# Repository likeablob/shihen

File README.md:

**SHIHEN** is a device which colors your everyday (a bit).  
Have a glimpse of your favorite poems, quotes or scenes of a movie.

## Features
- On board RTC offers 2+ years of battery life.([in theory](https://blc.now.sh/?config=eyJiYXR0ZXJ5Q2FwYWNpdHkiOiIzNTAiLCJzbGVlcEN1cnJlbnRNaWxpcyI6MC4wMDUsIndha2VDdXJyZW50TWlsaXMiOiI4MCIsIndha2V1cENvdW50IjoiMTIiLCJ3YWtldXBVbml0Ijo4NjQwMCwid2FrZXVwU2VjIjoiMSJ9))
- By using [a dedicated Web-based converter](https://shihen.now.sh/), you can quickly show any texts and videos on the device.

## Gallery
|    |  |
| :------------------------------------------------------------------------------: | :----------------------------------------------------------------------------: |
|  |  |
|    |                                                                                |

## Project structure
- [`pio/`](./pio) - code for the firmware(PlatformIO)
- [`kicad/`](./kicad) - PCB design (KiCad)
- [`openscad/`](./openscad) - models for the 3D-printable case. (OpenSCAD)
- https://github.com/likeablob/shihen-webui - code for the WebUI(Nuxt.js + Vuetify)

## Build Instructions
WIP

## BOM
WIP

## Refs
- Hackaday.io: https://hackaday.io/project/168039-shihen

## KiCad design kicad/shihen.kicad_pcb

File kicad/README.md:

# SHIHEN/PCB

## Prerequisites
- [KiCAD](http://kicad-pcb.org/) v5.0.1

## Credits
- [jdunmire]'s [ESP-12E.kicad_mod](./lib_ext/ESP-12E.kicad_mod): borrowed from [jdunmire/kicad-ESP8266](https://github.com/jdunmire/kicad-ESP8266/tree/70e6530de5e3cae4ae77a4bca7d73b20a0af6baf)
- [Joan_Sparky]'s [Conn_uSDcard.kicad_mod](./lib_ext/Conn_uSDcard.kicad_mod): borrowed from  https://forum.kicad.info/t/microsd-component-footprint-help/3095/5

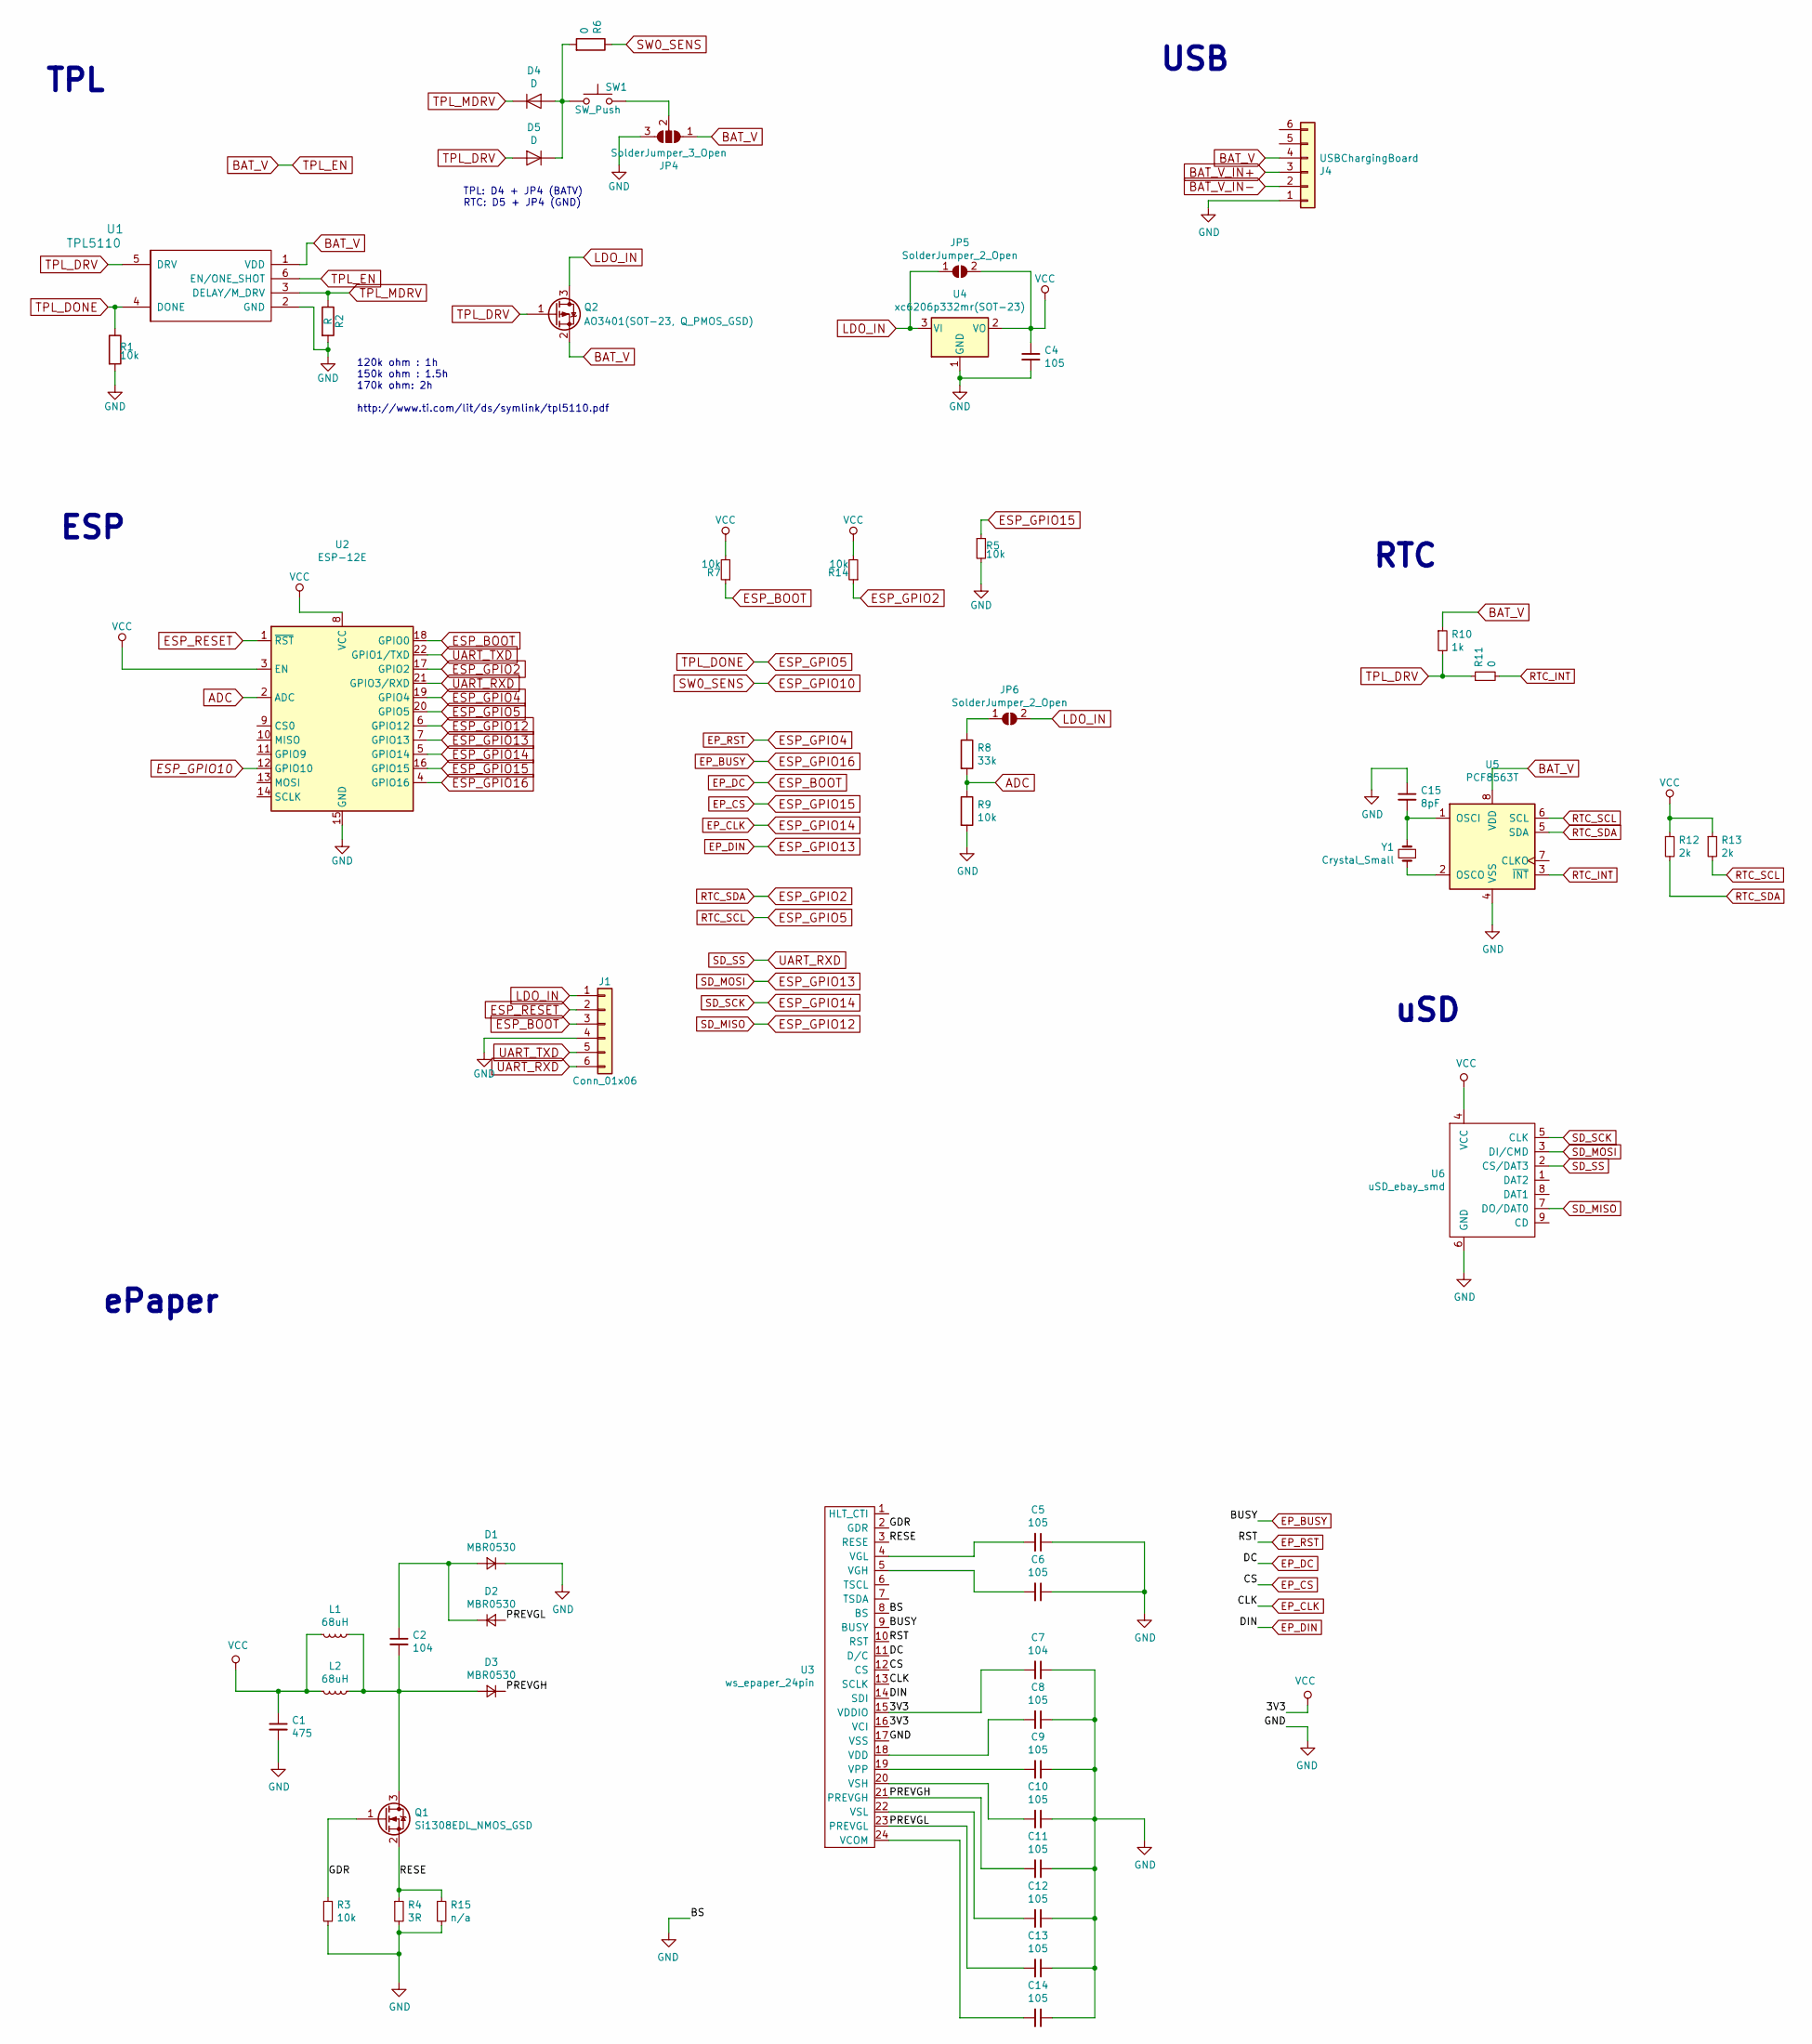
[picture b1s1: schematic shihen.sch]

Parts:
C1: 475; C_0805_2012Metric_Pad1.15x1.40mm_HandSolder; MPN CC0805KKX5R8BB475
C2, C7: 104; C_0805_2012Metric_Pad1.15x1.40mm_HandSolder; MPN C0805X104K101T
C4, C5, C6, C8, C9, C10, C11, C12, C13, C14: 105; C_0805_2012Metric_Pad1.15x1.40mm_HandSolder; MPN CC0805KKX7R8BB105
C15: 8pF; C_0805_2012Metric_Pad1.15x1.40mm_HandSolder; MPN 0805CG8R0C500NT
D1, D2, D3: MBR0530; D_SOD-123; MPN MBR0530
D4, D5: D; D_1206_3216Metric_Pad1.42x1.75mm_HandSolder; MPN LL4148ST
J1: Conn_01x06; PinHeader_1x06_P2.54mm_Vertical
J4: USBChargingBoard; USB_ChargingBoard
JP4: SolderJumper_3_Open; SolderJumper-3_P1.3mm_Open_RoundedPad1.0x1.5mm_NumberLabels
JP5, JP6: SolderJumper_2_Open; SolderJumper-2_P1.3mm_Open_RoundedPad1.0x1.5mm
L1: 68uH; L_6.3x6.3_H3
L2: 68uH; L_1206_3216Metric_Pad1.42x1.75mm_HandSolder; MPN NLCV32T-680K-PF
Q1: Si1308EDL_NMOS_GSD; SOT-323_SC-70_Handsoldering; MPN_disabled SI1308EDL-T1-GE3
Q2: AO3401(SOT-23, Q_PMOS_GSD); SOT-23_Handsoldering; MPN CJ2305
R1, R3, R5, R7, R9, R14: 10k; R_0805_2012Metric; MPN RC0805FR-0710KL
R2: R; R_0805_2012Metric
R4: 3R; R_0805_2012Metric; MPN 0805W8F300KT5E
R6, R11: 0; R_0805_2012Metric; MPN RC0805FR-070RL
R8: 33k; R_0805_2012Metric; MPN RC0805FR-0733KL
R10: 1k; R_0805_2012Metric; MPN RC0805JR-071KL
R12, R13: 2k; R_0805_2012Metric
R15: n/a; R_0805_2012Metric
SW1: SW_Push; SW_SPST_B3SL-1002P
U1: TPL5110; SOT-23-6_Handsoldering
U2: ESP-12E; MPN ESP-12E
U3: ws_epaper_24pin; Hirose_FH12-24S-0.5SH_1x24-1MP_P0.50mm_Horizontal_reverse; MPN FH12A-24S-0.5SH(55)
U4: xc6206p332mr(SOT-23); SOT-23_Handsoldering; MPN XC6206P332MR-G
U5: PCF8563T; SOIC-8_3.9x4.9mm_P1.27mm; MPN_disabled PCF8563T/5,518
U6: uSD_ebay_smd; Conn_uSDcard; MPN TF-01
Y1: Crystal_Small; Crystal_AT310_D3.0mm_L10.0mm_Horizontal_1EP_style1

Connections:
/GDR: Q1.1 (G), R3.1, U3.2 (GDR)
/PREVGH: C11.2, D3.1 (K), U3.21 (PREVGH)
/PREVGL: C13.2, D2.2 (A), U3.23 (PREVGL)
/RESE: Q1.2 (S), R4.1, R15.1, U3.3 (RESE)
ADC: R8.2, R9.1, U2.2 (ADC)
BAT_V: J4.4, JP4.1 (A), Q2.2 (S), R10.1, U1.1 (VDD), U1.6 (EN/ONE_SHOT), U5.8 (VDD)
BAT_V_IN+: J4.3
BAT_V_IN-: J4.2
EP_BUSY: U2.4 (GPIO16), U3.9 (BUSY)
EP_CLK: U2.5 (GPIO14), U3.13 (SCLK), U6.5 (CLK)
EP_CS: R5.1, U2.16 (GPIO15), U3.12 (CS)
EP_DC: J1.3, R7.1, U2.18 (GPIO0), U3.11 (D/C)
EP_DIN: U2.7 (GPIO13), U3.14 (SDI), U6.3 (DI/CMD)
EP_RST: U2.19 (GPIO4), U3.10 (RST)
ESP_GPIO2: R12.2, R14.1, U2.17 (GPIO2), U5.5 (SDA)
ESP_GPIO5: R1.1, R13.2, U1.4 (DONE), U2.20 (GPIO5), U5.6 (SCL)
ESP_GPIO10: R6.1, U2.12 (GPIO10)
ESP_GPIO12: U2.6 (GPIO12), U6.7 (DO/DAT0)
ESP_RESET: J1.2, U2.1 (~RST)
GND: C1.2, C4.2, C5.1, C6.1, C7.1, C8.1, C9.1, C10.1, C11.1, C12.1, C13.1, C14.1, C15.1, D1.1 (K), J1.4, J4.1, JP4.3 (B), R1.2, R2.2, R3.2, R4.2, R5.2, R9.2, R15.2, U1.2 (GND), U2.15 (GND), U3.8 (BS), U3.17 (VSS), U4.1 (GND), U5.4 (VSS), U6.6 (GND)
LDO_IN: J1.1, JP5.1 (A), JP6.2 (B), Q2.3 (D), U4.3 (VI)
unnamed: C2.1, D1.2 (A), D2.1 (K)
unnamed: C2.2, D3.2 (A), L1.1, L2.1, Q1.3 (D)
unnamed: C5.2, U3.4 (VGL)
unnamed: C6.2, U3.5 (VGH)
unnamed: C8.2, U3.18 (VDD)
unnamed: C9.2, U3.19 (VPP)
unnamed: C10.2, U3.20 (VSH)
unnamed: C12.2, U3.22 (VSL)
unnamed: C14.2, U3.24 (VCOM)
unnamed: C15.2, U5.1 (OSCI), Y1.2
unnamed: D4.2 (A), D5.1 (K), R6.2, SW1.1
unnamed: JP4.2 (C), SW1.2
unnamed: JP6.1 (A), R8.1
unnamed: U5.2 (OSCO), Y1.1
RTC_INT: R11.2, U5.3 (~INT~)
SD_SS: J1.6, U2.21 (GPIO3/RXD), U6.2 (CS/DAT3)
TPL_DRV: D5.2 (A), Q2.1 (G), R10.2, R11.1, U1.5 (DRV)
TPL_MDRV: D4.1 (K), R2.1, U1.3 (DELAY/M_DRV)
UART_TXD: J1.5, U2.22 (GPIO1/TXD)
VCC: C1.1, C4.1, C7.2, JP5.2 (B), L1.2, L2.2, R7.2, R12.1, R13.1, R14.2, U2.3 (EN), U2.8 (VCC), U3.15 (VDDIO), U3.16 (VCI), U4.2 (VO), U6.4 (VCC)

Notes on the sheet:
120k ohm : 1h 150k ohm : 1.5h 170k ohm: 2h http://www.ti.com/lit/ds/symlink/tpl5110.pdf
TPL: D4 + JP4 (BATV) RTC: D5 + JP4 (GND)
TPL
ESP
ePaper
USB
RTC
uSD

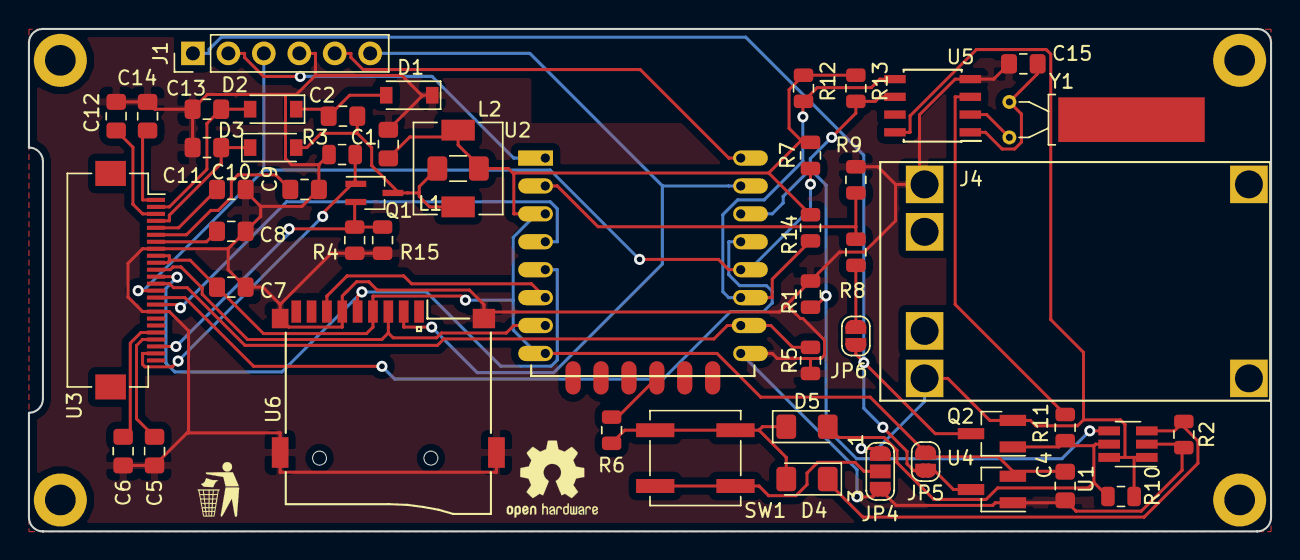
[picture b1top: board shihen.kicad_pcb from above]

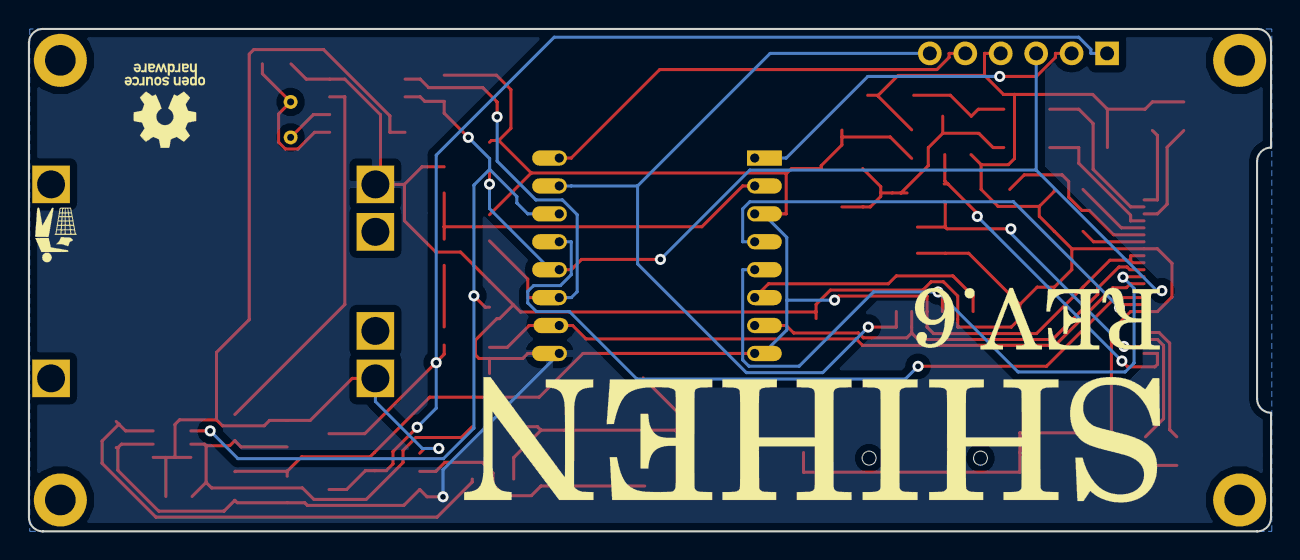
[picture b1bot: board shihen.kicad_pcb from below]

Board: 2 copper layers, 89.0 x 36.0 mm, 59 parts (3 on the bottom side), 39 nets.

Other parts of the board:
G1, G3: LOGO; gomi_5.7x5.7
G2: LOGO; shihen_logo_53x10
G4: OSHW-Logo_5.7x6mm_SilkScreen
MH1, MH2, MH3, MH4: MountingHole_2.2mm_M2_DIN965_Pad

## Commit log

2019-10-19 Add OpenSCAD files
2019-10-20 Add new image to the gallery
2019-10-20 Add KiCad, gerber files
2019-10-20 Add sources for the firmware
2019-10-20 Modify pio/README.md a bit
2019-10-20 Modify schemas - Add MPN(Fusion PCB's part number) as an attribute for PCBA - Fix some wrong constants
2019-10-20 Modify README - Fix typo - Add info about the ISP port
